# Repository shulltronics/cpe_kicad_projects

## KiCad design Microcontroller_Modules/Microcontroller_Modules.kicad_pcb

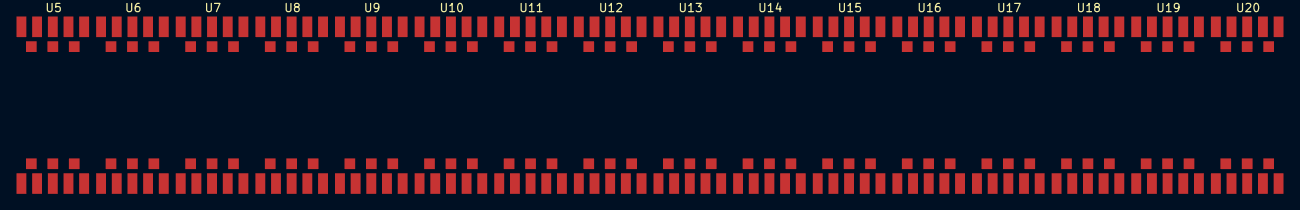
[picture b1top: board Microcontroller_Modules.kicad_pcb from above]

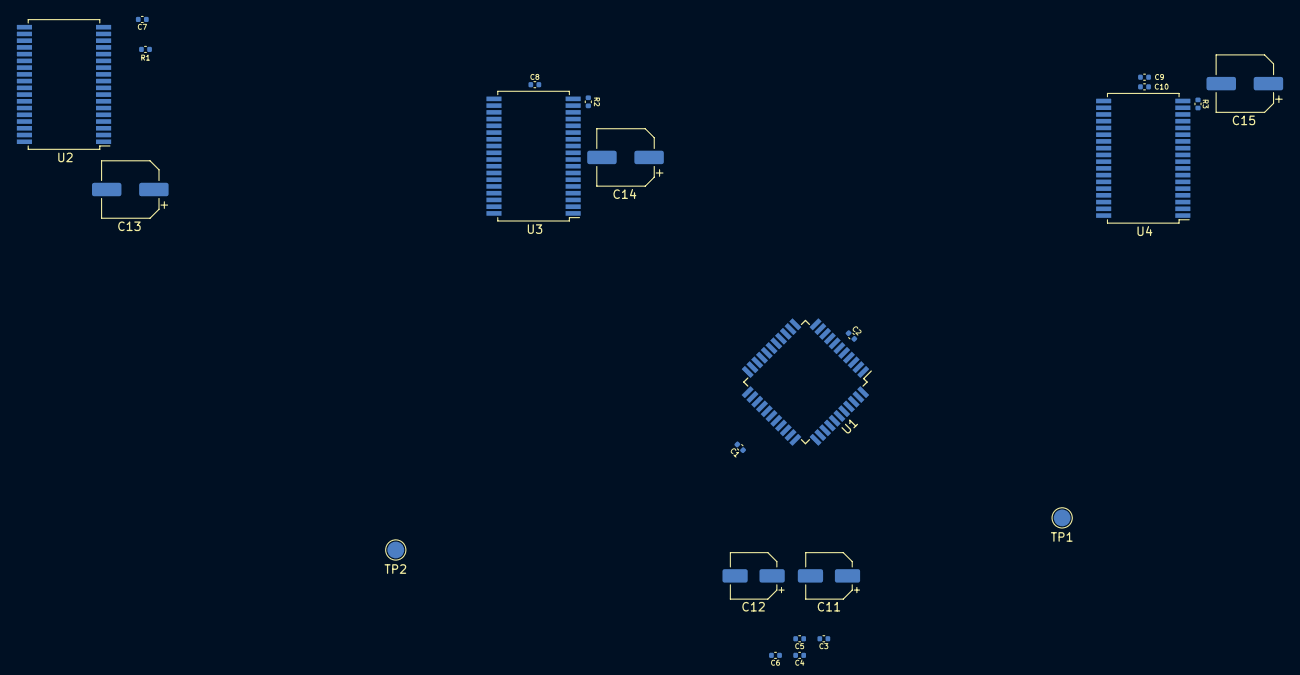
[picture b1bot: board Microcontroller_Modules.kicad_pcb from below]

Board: 2 copper layers, 40 parts (24 on the bottom side), 47 nets, no tracks yet.

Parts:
C1, C2, C3, C4, C5, C6, C7, C8, C9: CpE-3001_Capacitor_0.1uF_0402; CpE-3001_0402
C10: CpE-3007_Capacitor_22pF_50V_0402; CpE-3007_0402
C11, C12: CpE-3009_10uF_50V_5.0mm; CpE_3009_10uF_50V_5.0mm_SMD
C13, C14, C15: CpE-3010_47uF_35V_6.3mm; CpE-3010_47uF_35V_6.3mm_SMD
R1, R2, R3: CpE-3008_56k_0.0625W_1%_0402; CpE-3008_0402
TP1: OSC_OUT; CpE_TP_D2.0mm
TP2: BLINK; CpE_TP_D2.0mm
U1: CpE-3002_PIC18F47K40; CpE-3002_TQFP-44_10x10mm_P0.8mm
U2, U3, U4: CpE-3003_MAX6954; CpE-3003_MAX6954AAX
U5, U6, U7, U8, U9, U10, U11, U12, U13, U14, U15, U16, U17, U18, U19, U20: CpE-3006_14SEG_GRN_CC

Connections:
/display/BLINK: TP2.1, U2.32, U3.32, U4.32
/display/DC1: U3.6, U4.4
/display/DC2: U2.6, U3.4
/display/DIGIT0: U4.7, U4.9, U4.11, U4.13, U5.7, U5.10, U5.11, U5.14, U6.7, U6.10, U6.11, U7.7, U7.10, U7.11, U7.14, U8.7, U8.10, U8.11, U9.7, U9.10, U9.11, U9.14, U10.7, U10.10, U10.11, U11.7, U11.10, U11.11, U11.14, U12.7, U12.10, U12.11
/display/DIGIT1: U4.8, U6.14
/display/DIGIT3: U4.10, U4.12, U5.6, U6.6, U7.6, U8.6, U8.14, U9.6, U10.6, U10.14, U11.6, U12.6
/display/DIGIT7: U4.14, U12.14
/display/DIGIT9: U3.8, U14.14
/display/DIGIT10: U3.7, U3.9, U3.11, U3.13, U13.7, U13.10, U13.11, U13.14, U14.7, U14.10, U14.11, U15.7, U15.10, U15.11, U15.14, U16.7, U16.10, U16.11, U17.7, U17.10, U17.11, U17.14, U18.7, U18.10, U18.11, U19.7, U19.10, U19.11, U19.14, U20.7, U20.10, U20.11
/display/DIGIT11: U3.10, U3.12, U13.6, U14.6, U15.6, U16.6, U16.14, U17.6, U18.6, U18.14, U19.6, U20.6
/display/DIGIT15: U3.14, U20.14
/display/DIGIT16: U2.7, U2.9, U2.11, U2.13
/display/DIGIT19: U2.10, U2.12
/display/GRP0_ISET: R3.2, U4.17
/display/GRP0_P3: U4.35, U4.36
/display/GRP0_SEGDP: U4.31, U5.5, U6.5, U7.5, U8.5, U9.5, U10.5, U11.5, U12.5
/display/GRP0_SEGE: U4.15, U5.8, U6.8, U7.8, U8.8, U9.8, U10.8, U11.8, U12.8
/display/GRP0_SEGF: U4.22, U5.16, U6.16, U7.16, U8.16, U9.16, U10.16, U11.16, U12.16
/display/GRP0_SEGG1: U4.23, U5.1, U6.1, U7.1, U8.1, U9.1, U10.1, U11.1, U12.1
/display/GRP0_SEGG2: U4.24, U5.12, U6.12, U7.12, U8.12, U9.12, U10.12, U11.12, U12.12
/display/GRP0_SEGH: U4.25, U5.9, U6.9, U7.9, U8.9, U9.9, U10.9, U11.9, U12.9
/display/GRP0_SEGI: U4.26, U5.15, U6.15, U7.15, U8.15, U9.15, U10.15, U11.15, U12.15
/display/GRP0_SEGJ: U4.27, U5.13, U6.13, U7.13, U8.13, U9.13, U10.13, U11.13, U12.13
/display/GRP0_SEGK: U4.28, U5.4, U6.4, U7.4, U8.4, U9.4, U10.4, U11.4, U12.4
/display/GRP0_SEGL: U4.29, U5.3, U6.3, U7.3, U8.3, U9.3, U10.3, U11.3, U12.3
/display/GRP0_SEGM: U4.30, U5.2, U6.2, U7.2, U8.2, U9.2, U10.2, U11.2, U12.2
/display/GRP1_ISET: R2.2, U3.17
/display/GRP1_P3: U3.35, U3.36
/display/GRP1_SEGDP: U3.31, U13.5, U14.5, U15.5, U16.5, U17.5, U18.5, U19.5, U20.5
/display/GRP1_SEGE: U3.15, U13.8, U14.8, U15.8, U16.8, U17.8, U18.8, U19.8, U20.8
/display/GRP1_SEGF: U3.22, U13.16, U14.16, U15.16, U16.16, U17.16, U18.16, U19.16, U20.16
/display/GRP1_SEGG1: U3.23, U13.1, U14.1, U15.1, U16.1, U17.1, U18.1, U19.1, U20.1
/display/GRP1_SEGG2: U3.24, U13.12, U14.12, U15.12, U16.12, U17.12, U18.12, U19.12, U20.12
/display/GRP1_SEGH: U3.25, U13.9, U14.9, U15.9, U16.9, U17.9, U18.9, U19.9, U20.9
/display/GRP1_SEGI: U3.26, U13.15, U14.15, U15.15, U16.15, U17.15, U18.15, U19.15, U20.15
/display/GRP1_SEGJ: U3.27, U13.13, U14.13, U15.13, U16.13, U17.13, U18.13, U19.13, U20.13
/display/GRP1_SEGK: U3.28, U13.4, U14.4, U15.4, U16.4, U17.4, U18.4, U19.4, U20.4
/display/GRP1_SEGL: U3.29, U13.3, U14.3, U15.3, U16.3, U17.3, U18.3, U19.3, U20.3
/display/GRP1_SEGM: U3.30, U13.2, U14.2, U15.2, U16.2, U17.2, U18.2, U19.2, U20.2
/display/GRP2_ISET: R1.2, U2.17
/display/GRP2_P3: U2.35, U2.36
/display/OSC: C10.2, U4.20
/display/OSC_TIE: TP1.1, U2.20, U3.20, U4.33
/display/UI_CS: U2.3, U3.3, U4.3
/display/UI_SCK: U2.5, U3.5, U4.5
GND: C1.2, C2.2, C3.2, C4.2, C5.2, C6.2, C7.2, C8.2, C9.2, C10.1, C11.2, C12.2, C13.2, C14.2, C15.2, R1.1, R2.1, R3.1, U2.16, U2.18, U3.16, U3.18, U4.16, U4.18
VCC: C1.1, C2.1, C3.1, C4.1, C5.1, C6.1, C7.1, C8.1, C9.1, C11.1, C12.1, C13.1, C14.1, C15.1, U2.19, U2.21, U3.19, U3.21, U4.19, U4.21

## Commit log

2021-11-23 Progress on LED display board
2022-02-25 Added PCIe-x4 template
